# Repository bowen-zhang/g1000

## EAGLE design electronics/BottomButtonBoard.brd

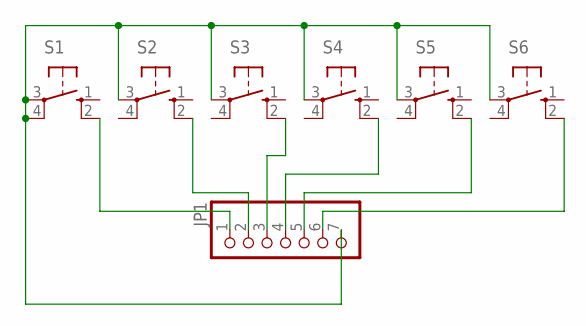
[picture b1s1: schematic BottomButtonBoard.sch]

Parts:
JP1: PINHD-1X7; 1X07
S1, S2, S3, S4, S5, S6: 10-XX; B3F-10XX

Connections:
unnamed: JP1.1, S1.2 (S1)
unnamed: JP1.2, S2.2 (S1)
unnamed: JP1.3, S3.2 (S1)
unnamed: JP1.4, S4.2 (S1)
unnamed: JP1.5, S5.2 (S1)
unnamed: JP1.6, S6.2 (S1)
unnamed: JP1.7, S1.3, S1.4 (P1), S2.3, S3.3, S4.3, S5.3, S6.3

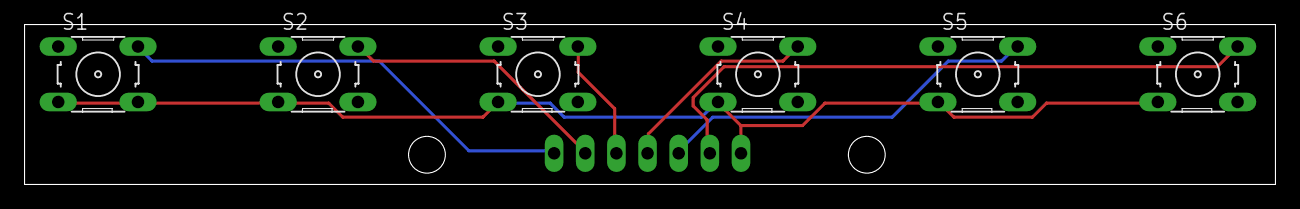
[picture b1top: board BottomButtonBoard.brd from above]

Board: 2 copper layers, 102.0 x 13.0 mm, 7 parts (1 on the bottom side), 7 nets.

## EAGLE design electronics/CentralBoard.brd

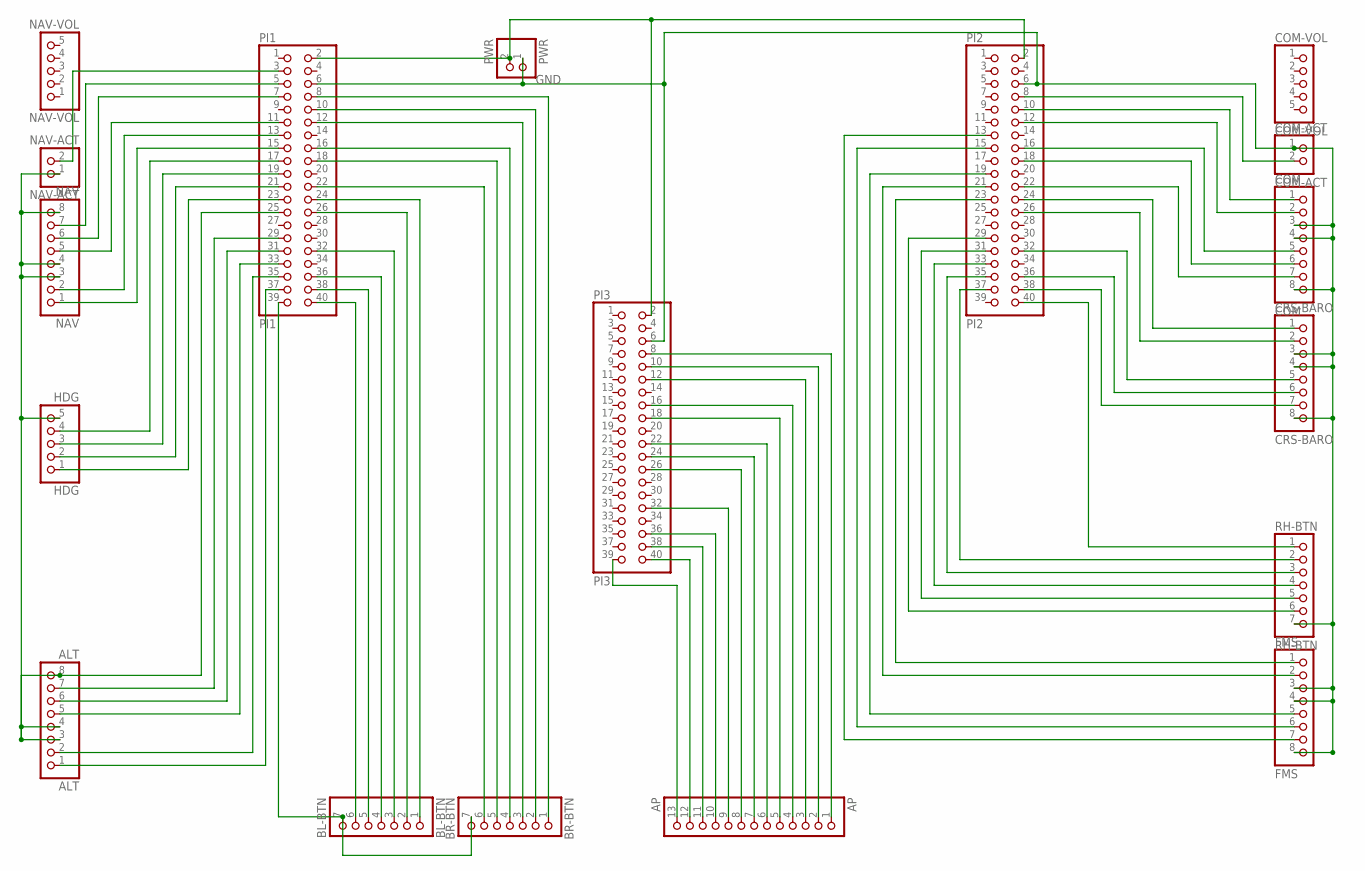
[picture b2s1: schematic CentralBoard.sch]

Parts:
ALT: ALT; 1X08/90
AP: AP; 1X13
BL-BTN: BL-BTN; 1X07/90
BR-BTN: BR-BTN; 1X07
COM: COM; 1X08/90
COM-ACT: COM-ACT; 1X02/90
COM-VOL: COM-VOL; 1X05/90
CRS-BARO: CRS-BARO; 1X08/90
FMS: FMS; 1X08/90
HDG: HDG; 1X05/90
NAV: NAV; 1X08/90
NAV-ACT: NAV-ACT; 1X02/90
NAV-VOL: NAV-VOL; 1X05/90
PI1: PI1; 2X20
PI2: PI2; 2X20
PI3: PI3; 2X20
PWR: PWR; 1X02/90
RH-BTN: RH-BTN; 1X07/90

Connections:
GND: COM.3, COM.4, COM.8, COM-ACT.1, CRS-BARO.3, CRS-BARO.4, CRS-BARO.8, FMS.3, FMS.4, FMS.8, PI1.6, PI2.6, PI3.6, PWR.1, RH-BTN.7
unnamed: CRS-BARO.6, PI2.36
unnamed: HDG.3, PI1.19
unnamed: BL-BTN.7, BR-BTN.7, PI1.39
unnamed: CRS-BARO.7, PI2.38
unnamed: BL-BTN.6, PI1.40
unnamed: BL-BTN.5, PI1.38
unnamed: ALT.7, PI1.29
unnamed: ALT.3, ALT.4, ALT.8, HDG.5, NAV.3, NAV.4, NAV.8, NAV-ACT.1, PI1.25
unnamed: NAV.7, PI1.5
unnamed: NAV.6, PI1.7
unnamed: NAV.2, PI1.13
unnamed: NAV.1, PI1.15
unnamed: NAV.5, PI1.11
unnamed: HDG.2, PI1.21
unnamed: HDG.1, PI1.23
unnamed: COM.2, PI2.12
unnamed: ALT.6, PI1.31
unnamed: ALT.5, PI1.33
unnamed: ALT.2, PI1.35
unnamed: ALT.1, PI1.37
unnamed: NAV-ACT.2, PI1.3
unnamed: BR-BTN.6, PI1.22
unnamed: BR-BTN.5, PI1.18
unnamed: HDG.4, PI1.17
unnamed: BL-BTN.4, PI1.36
unnamed: BL-BTN.3, PI1.32
unnamed: BL-BTN.2, PI1.26
unnamed: BL-BTN.1, PI1.24
unnamed: BR-BTN.4, PI1.16
unnamed: BR-BTN.3, PI1.12
unnamed: BR-BTN.2, PI1.10
unnamed: BR-BTN.1, PI1.8
unnamed: COM.1, PI2.10
unnamed: COM-ACT.2, PI2.8
unnamed: PI2.31, RH-BTN.5
unnamed: FMS.2, PI2.21
unnamed: PI2.29, RH-BTN.6
unnamed: AP.2, PI3.10
unnamed: AP.3, PI3.12
unnamed: AP.1, PI3.8
unnamed: CRS-BARO.1, PI2.24
unnamed: CRS-BARO.2, PI2.26
unnamed: CRS-BARO.5, PI2.32
unnamed: AP.4, PI3.16
unnamed: FMS.5, PI2.19
unnamed: AP.5, PI3.18
unnamed: AP.6, PI3.22
unnamed: PI2.40, RH-BTN.1
unnamed: PI2.37, RH-BTN.2
unnamed: PI2.35, RH-BTN.3
unnamed: PI2.33, RH-BTN.4
unnamed: AP.7, PI3.24
unnamed: FMS.1, PI2.23
unnamed: AP.8, PI3.26
unnamed: AP.9, PI3.32
unnamed: FMS.6, PI2.15
unnamed: FMS.7, PI2.13
unnamed: AP.10, PI3.36
unnamed: AP.11, PI3.38
unnamed: AP.12, PI3.40
unnamed: AP.13, PI3.39
unnamed: PI1.2, PI2.2, PI3.2, PWR.2
unnamed: COM.5, PI2.16
unnamed: COM.6, PI2.18
unnamed: COM.7, PI2.22

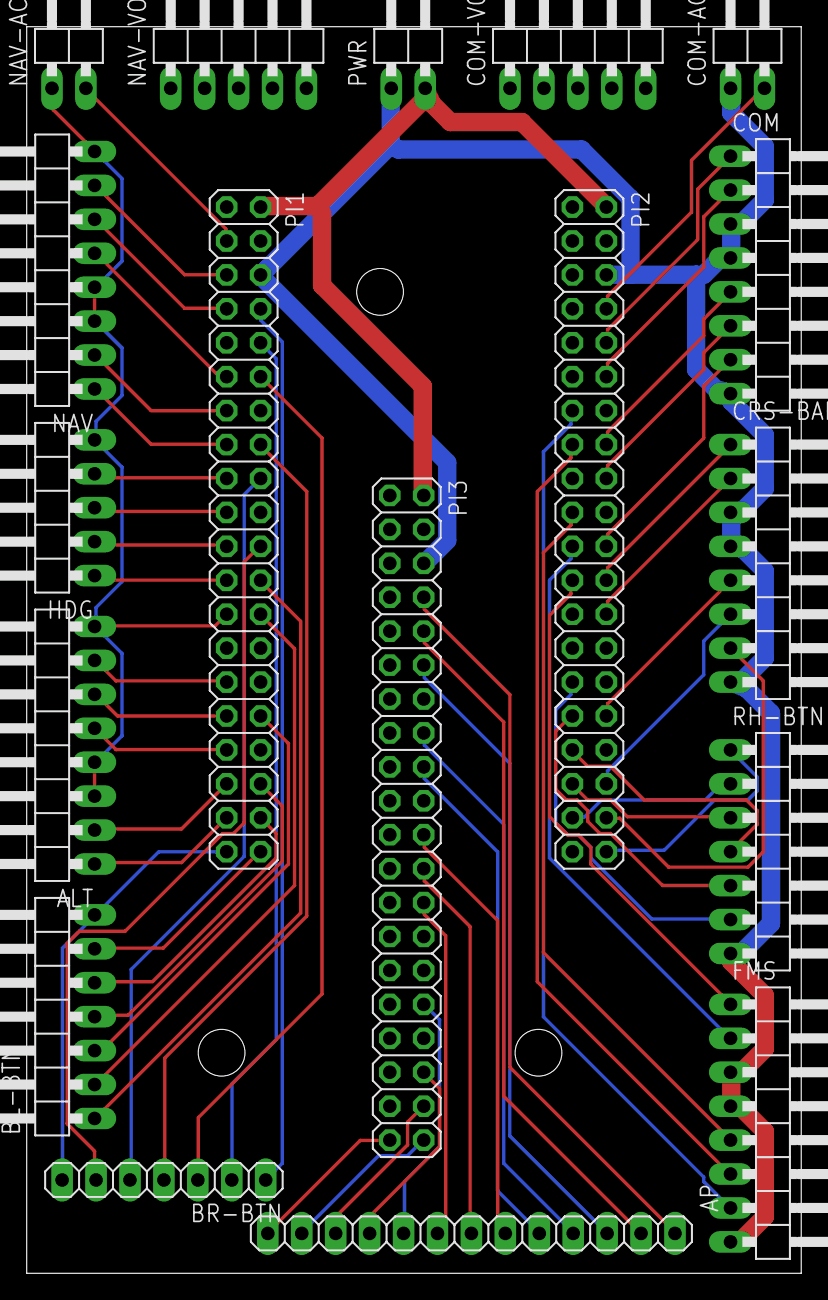
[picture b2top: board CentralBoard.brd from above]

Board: 2 copper layers, 58.0 x 93.3 mm, 18 parts (0 on the bottom side), 66 nets.

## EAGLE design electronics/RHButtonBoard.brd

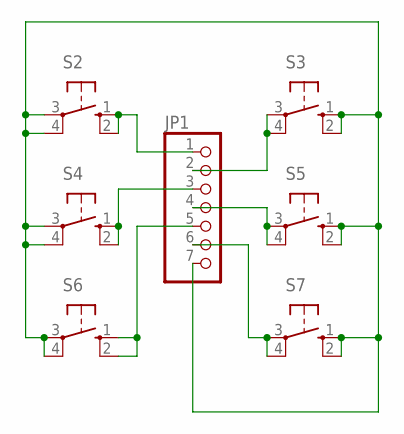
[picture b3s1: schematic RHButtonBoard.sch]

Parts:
JP1: PINHD-1X7; 1X07
S2, S3, S4, S5, S6, S7: 10-XX; B3F-10XX

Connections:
unnamed: JP1.1, S2.1 (S), S2.2 (S1)
unnamed: JP1.2, S3.3, S3.4 (P1)
unnamed: JP1.3, S4.1 (S), S4.2 (S1)
unnamed: JP1.4, S5.3, S5.4 (P1)
unnamed: JP1.5, S6.1 (S), S6.2 (S1)
unnamed: JP1.6, S7.3, S7.4 (P1)
unnamed: JP1.7, S2.3, S2.4 (P1), S3.1 (S), S3.2 (S1), S4.3, S4.4 (P1), S5.1 (S), S5.2 (S1), S6.3, S6.4 (P1), S7.1 (S), S7.2 (S1)

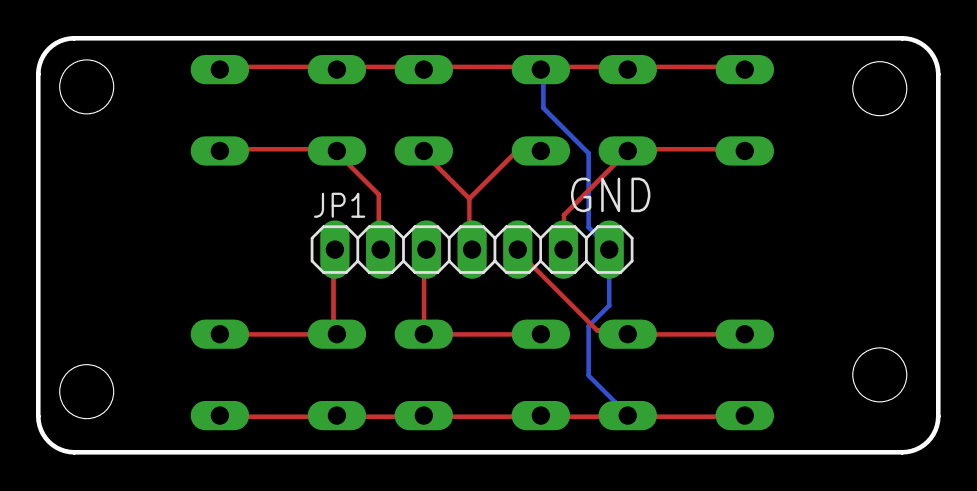
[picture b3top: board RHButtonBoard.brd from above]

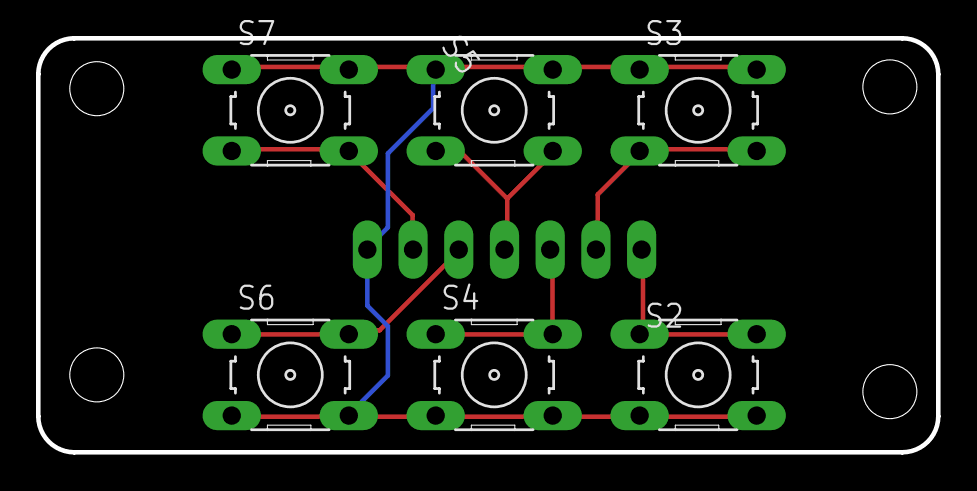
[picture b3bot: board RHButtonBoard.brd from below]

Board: 2 copper layers, 50.0 x 23.0 mm, 7 parts (6 on the bottom side), 7 nets.

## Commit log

2019-01-21 init
2019-01-24 adds Eagle files for PCBs
2019-01-26 update pin mapping for PFD 1
2019-01-27 add config for MFD
2019-02-02 update pfd1 config
2019-02-03 Have GPIO callback and sim proxy call in separate threads so network delay won't mess up GPIO signal handling.
